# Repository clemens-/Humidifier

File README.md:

# Automatic cigar humidifier
This is a device to control the humidity in a humidor for storing cigars.

## The idea
I enjoy smoking a cigar from time to time. However, cigars need to be stored at a controlled humidity level until it is time to enjoy them. So, I bought a cheap humidor with a passive element in it for just that. A passive element works be releasing humidity until a certain relative humidity is reached but can also absorb excess humidity. In my case, this did not work properly: the foam would never reach the desired percentage of relative humidity. Thus, I set out to solve this issue.
## Defining requirements
I first defined some requirements before starting anything:
* The relative humidity should be actively controlled.
* The device should fit inside the humidor.
* If the humidity cannot be controlled for whatever reason, the user shall notice.
* No batteries to worry about.
## The solution
The device I built uses a humidity sensor (the SHT-31 by Sensirion), a fan and a piece of foam soaked in distilled water. If the sensor notices that the humidity drops below a certain threshold, the fan is switched on. It blows air over the wet foam, thus humidifying the air and raising the humidity inside the humidor. After the upper humidity threshold is reached, the fan is switched off. An integrated speaker alerts the user if the humidity cannot be raised after a certain time. The humidifier fits inside the humidor and is powered by a 5V USB charger, plugged into an outlet near the humidor.

## Testing
I have been using the humidifier in my humidor for about 6 months now with two Sensirion humidity and temperature measurements devices in the two compartments. The relative humidity setpoint is at 77%. As you can see below, this is kept quite closely.

## Improvements
I already noticed some possible improvements, but did not implement them as the humidifier works quite well:
1. The alarm is not often triggered, hence not that noticeable. However, triggering the alarm more often could be very annoying, as there is nothing in there preventing it from going off at 2 in the morning.
2. The fan control is only ON-OFF. A PWM control would help in making the device a bit quieter than it currently is. It is not loud, but noticeable in a quiet room.
3. The foam I used is not very absorbable. Thus, when filling the funnel in the back, the water runs over the foam and into the rest of the enclosure. A more absorbable foam should resolve that. Alternatively, extending the funnel into the foam would allow a more controlled water path.
## What is in the repository?
I documented my work here and I think it should be self-explanatory. Here is an overview:
### BOM
The bill of materials lists all the material used for building the humidifier. For the fan, just use any generic 30mm 5V fan. I got mine of AliExpress.
### Enclosure
The enclosure I designed holds the fan, PCB and the piece of 50mmx10mm foam I used to store the distilled water. It consists of the following parts:
* The cover clips into the enclosure and has a funnel to soak the foam without taking the cover off.
* The enclosure which has stubs to mount the fan, the PCB and the foam.
* Standoffs I needed to lift the PCB after I realised that it was sitting too low.

All are available as STLs, so you can directly 3D print them. I also included the Fusion 360 project as an F3Z file. I printed the parts on my Cetus 3D and they turned out great, with the clipping action holding up to several cycles so far.
### Images
Some images of the humidifier. They are also used in this readme.
### PCB
Contains the Gerber and NG Drill files you need if you want to build this humidifier.
### Schematics
The schematic is stored here. If you open it in Adobe Reader, you can even click the parts to reveal more information.
### Software
The Arduino software is stored here. You will need to load the Arduino bootloader onto the ATiny85 before using it. Check [SpenceKonde's ATTinyCore](https://github.com/SpenceKonde/ATTinyCore) on how to do this.

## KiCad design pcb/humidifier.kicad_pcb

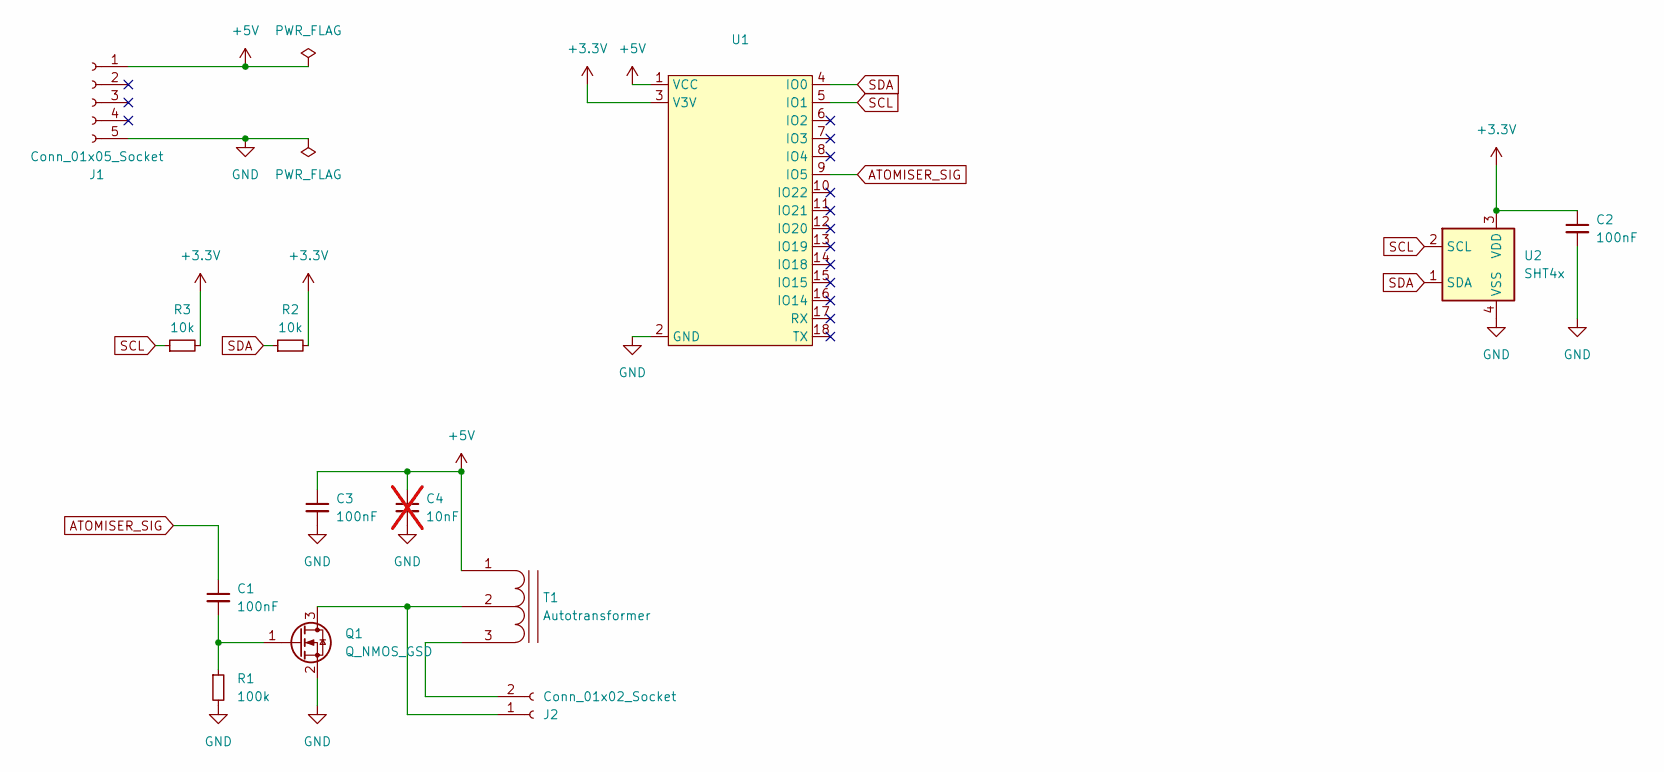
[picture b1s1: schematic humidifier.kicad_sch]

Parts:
C1, C2, C3: 100nF; C_0805_2012Metric_Pad1.18x1.45mm_HandSolder
C4: 10nF; C_0805_2012Metric_Pad1.18x1.45mm_HandSolder; not fitted
J1: Conn_01x05_Socket; FFC_1x05_P2.00mm_Horizontal
J2: Conn_01x02_Socket; JST_XH_B2B-XH-A_1x02_P2.50mm_Vertical
Q1: Q_NMOS_GSD; SOT-23_Handsoldering
R1: 100k; R_0805_2012Metric_Pad1.20x1.40mm_HandSolder
R2, R3: 10k; R_0805_2012Metric_Pad1.20x1.40mm_HandSolder
T1: Autotransformer; CP_Radial_D7.5mm_P2.50mm
U1: Waveshare-ESP32-C6-Zero
U2: SHT4x; Sensirion_DFN-4_1.5x1.5mm_P0.8mm_SHT4x_NoCentralPad

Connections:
+3.3V: C2.1, R2.2, R3.2, U1.3 (V3V), U2.3 (VDD)
+5V: C3.1, C4.1, J1.1, T1.1 (PR1), U1.1 (VCC)
ATOMISER_SIG: C1.1, U1.9 (IO5)
GND: C2.2, C3.2, C4.2, J1.5, Q1.2 (S), R1.2, U1.2 (GND), U2.4 (VSS)
unnamed: J2.1, Q1.3 (D), T1.2 (PM)
unnamed: J2.2, T1.3 (PR2)
unnamed: C1.2, Q1.1 (G), R1.1
SCL: R3.1, U1.5 (IO1), U2.2 (SCL)
SDA: R2.1, U1.4 (IO0), U2.1 (SDA)

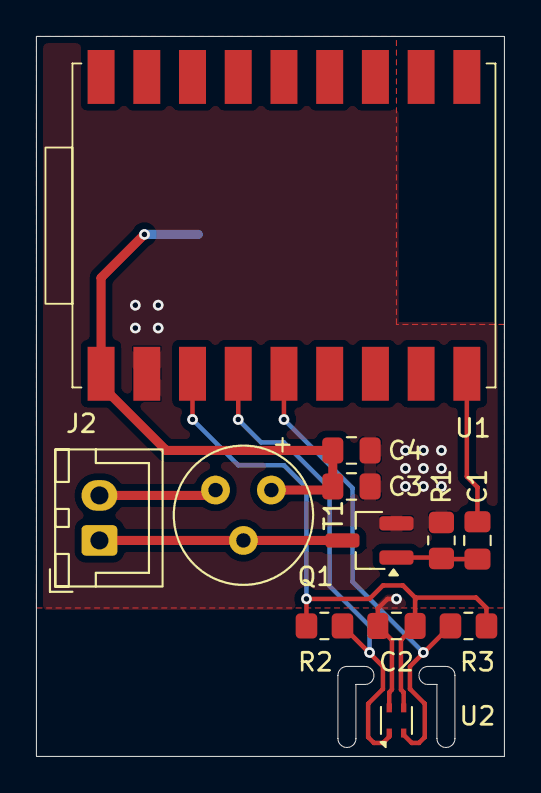
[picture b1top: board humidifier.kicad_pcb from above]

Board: 2 copper layers, 26.0 x 40.0 mm, 13 parts (1 on the bottom side), 9 nets.

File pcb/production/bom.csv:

Designator,Footprint,Quantity,Value,LCSC Part #
"C1, C2, C3",0805,3,100nF,
J1,FFC_1x05_P2.00mm_Horizontal,1,Conn_01x05_Socket,
J2,JST_XH_B2B-XH-A_1x02_P2.50mm_Vertical,1,Conn_01x02_Socket,
Q1,SOT-23_Handsoldering,1,Q_NMOS_GSD,
R1,0805,1,100k,
"R2, R3",0805,2,10k,
T1,CP_Radial_D7.5mm_P2.50mm,1,Autotransformer,
U1,Waveshare-ESP32-C6-Zero,1,~,
U2,Sensirion_DFN-4_1.5x1.5mm_P0.8mm_SHT4x_NoCentralPad,1,SHT4x,

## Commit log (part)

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2024-02-17 Solution with piezo-humidifier
